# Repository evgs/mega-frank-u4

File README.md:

# MEGAFRANK 1.02-U4
MegaFRANK is a hardware emulation platform built around the Raspberry Pi RP2350 QFN module

## DISCLAIMER 
This megafrank-u4 board is a sub-fork from https://github.com/rh1tech/frank repository originally designed by [Mikhail Matveev](https://github.com/xtremespb), [r1tech](https://github.com/rh1tech)

## Changes
- Two stacked USB-A ports were added on front board edge. 4 USB-A host ports total
- Power barrel 5mm connector was moved to right edge of the board
- ESP-RESET connected to PGPIO36 (optional, available if S11 jumper is closed) 

## DIP Switches S1 description
| Switch | Function                                                   |
| ------ | ---------------------------------------------------------- |
| TDA    | Sound path through I2S TDA (On) or PWM (Off)               |
| TS     | Enable TurboSound path (On)                                |
| TAPE   | Connect TAPE IN analog input to RP2540B                    |
| MONO   | Mono (On) of Stereo (Off) sound path                       |
| MPU    | Enable +3V3 external pullup on GPIO0/1 (Mouse/UART port)   |
| SHDN   | Shutdown (On) speaker amplifier PAM8403 (outputs J13, J14) |

## TDA/TS switches useful combinations
| TDA    | TS     | Output selected        |
| ------ | ------ | ---------------------- |
| off    | off    | RP2350 PWM             |
| **ON** | off    | I2S TDA1387T           |
| off    | **ON** | Turbosound 2xAY-3-8910 |
| **ON** | **ON** | Output Disabled        |

Please read detailed docs in original project [FRANK repository](https://github.com/rh1tech/frank)

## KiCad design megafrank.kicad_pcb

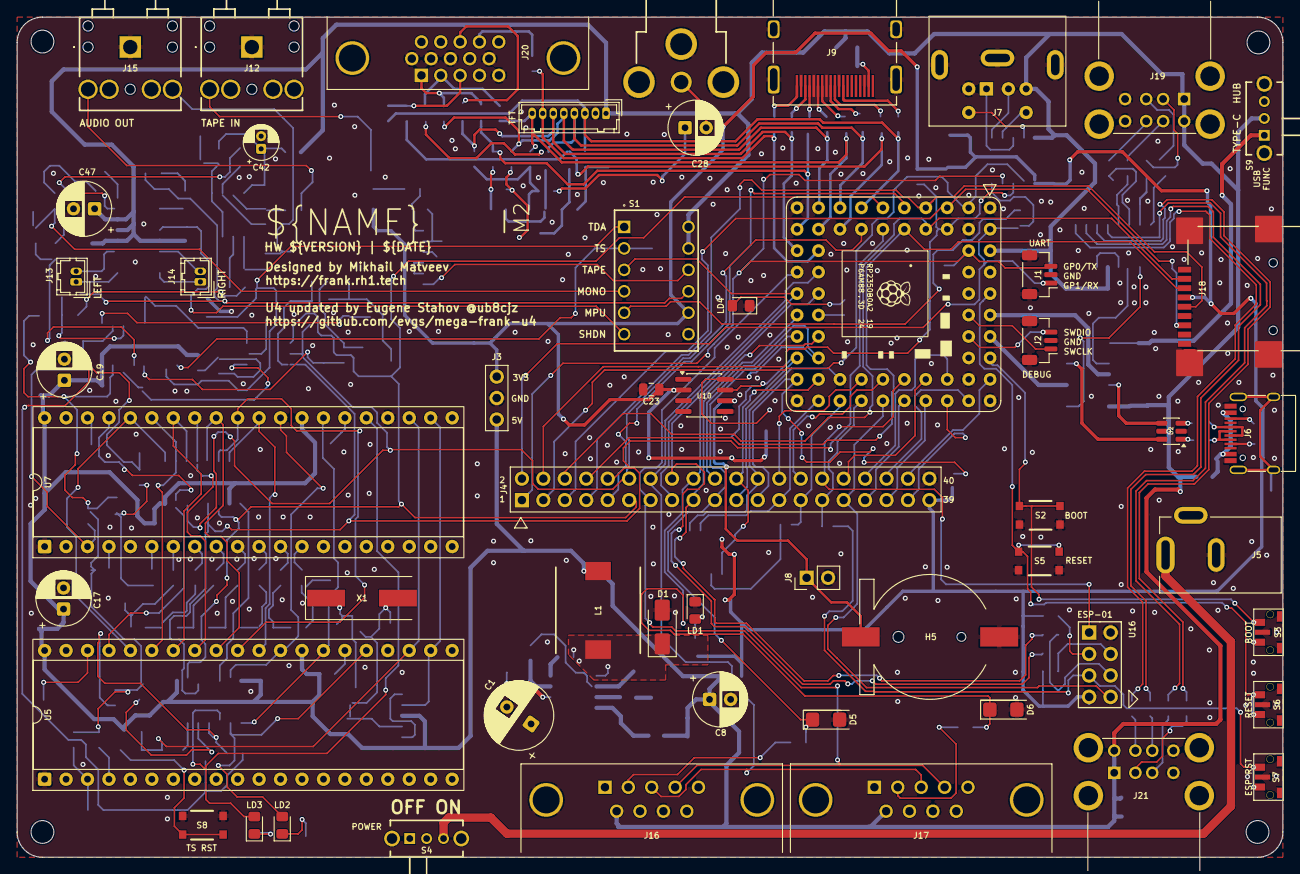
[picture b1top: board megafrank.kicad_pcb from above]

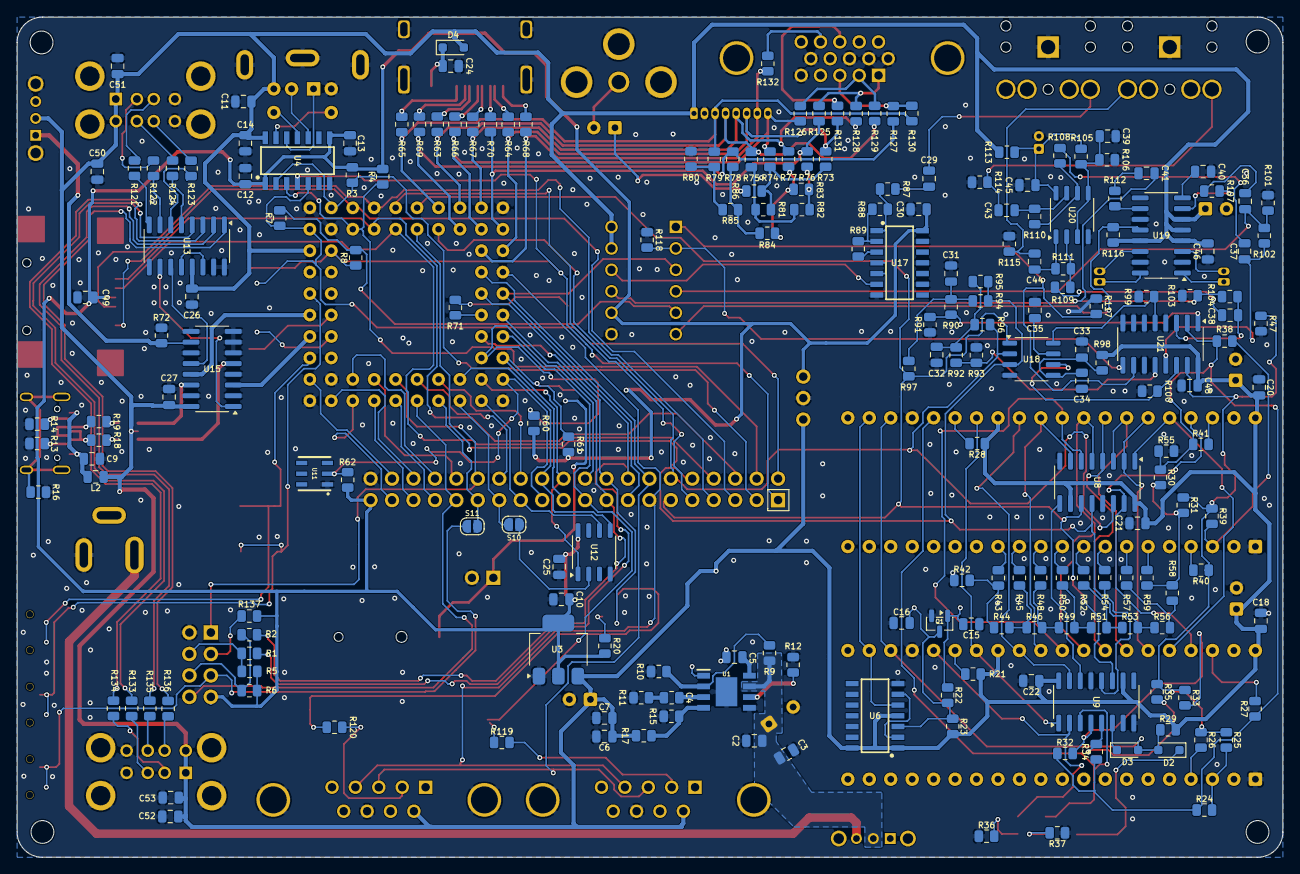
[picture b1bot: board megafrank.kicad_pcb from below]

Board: 2 copper layers, 149.9 x 99.5 mm, 262 parts (204 on the bottom side), 223 nets.

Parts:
C1: 680u; C_Radial_D8.0mm_P3.50mm
C2, C7, C10, C33, C35, C37, C38, C39, C43, C44, C50, C51, C52, C53: 10u; C_0805_2012Metric
C3, C5, C6, C9, C11, C12, C13, C14, C18, C20, C21, C22, C23, C24, C25, C27, C29, C30, C34, C40, C45, C48, C49: 100n; C_0805_2012Metric
C4: 150pF; R_0805_2012Metric
C8, C28: 220u; C_Radial_D6.3mm_P2.50mm
C15, C16: 22p; C_0805_2012Metric
C17, C19, C47: 100u; C_Radial_D6.3mm_P2.50mm
C26: 4.7u; C_0805_2012Metric
C31, C32: 47n; C_0805_2012Metric
C36, C41, C46: 1u; C_0805_2012Metric
C42: 10u; CP_Radial_D4.0mm_P1.50mm
D1: 1N5822; D_SMA
D2, D3: 1N4148; D_SOD-323
D4: 1N5819WS; D_SOD-323
D5, D6: 3V3; D_MiniMELF
H1, H2, H3, H4: Hole 2.7mm; MountingHole_2.7mm
H5: Battery_CR1220
J1: UART; JST_SH_1x03_P1.00mm_Vertical
J2: DEBUG; JST_SH_1x03_P1.00mm_Vertical
J3: PWR; PinHeader_1x03_P2.54mm
J4: Conn_02x20_Odd_Even; PinHeader_2x20_P2.54mm_Vertical
J5: DC-005-5A-2.0; BarrelJack_DC-005
J6: USB4215-03-A; USB_C_Receptacle
J7: MDC-036; MiniDIN_6pin_Female
J8: BAT 3V; PinHeader_1x02_P2.54mm_Vertical
J9: DC3RX19JA2; HDMI_Female
J10: RCA-103; BarrelJack_RCJ-012
J11: Pin Header 1x08; JST_GH_1x08_P1.25mm
J12, J15: SJ1-3525N; AudioJack_3.5mm_SJ1-3525N
J13: PAM L; JST_GH_1x02_P1.25mm
J14: PAM R; JST_GH_1x02_P1.25mm
J16, J17: GP2; DSUB-9_Male_TopMount
J18: 104031-0811; MicroSD_SMD_Long
J19, J21: SS-52100-004; USB_A_Stacked
J20: VGA; DSUB-15_Female
L1: 22uH; Inductor_CDRH104RNP
L2: 330R; C_0805_2012Metric
LD1: Green; LED_0805
LD2, LD3: Orange; LED_0805
LD4: Blue; LED_0805
Q1: BC850; SOT-23
R1, R2, R20, R21, R23, R28, R36, R37, R71, R96, R97, R119, R120, R128, R129, R130: 1K; R_0805_2012Metric
R3, R4, R5, R6, R7, R8, R29, R30, R31, R32, R33, R34, R35, R44, R46, R49, R51, R53, R56, R58, R72, R90, R92, R101, R102, R103, R104, R105, R106, R107, R108, R109, R112, R116, R117, R118, R137: 10K; R_0805_2012Metric
R9, R11, R12, R22, R88, R89: 100K; R_0805_2012Metric
R10: 24K; R_0805_2012Metric
R13, R14: 5.1K; R_0805_2012Metric
R15: 8.2K; R_0805_2012Metric
R16: 1M; R_0805_2012Metric
R17: 43K; R_0805_2012Metric
R18, R19, R121, R122, R123, R124, R133, R134, R135, R136: 22R; R_0805_2012Metric
R24, R25, R38, R39, R60, R61, R62, R87: 4.7K; R_0805_2012Metric
R26, R27, R40, R41, R91, R93, R94, R95: 2K; R_0805_2012Metric
R42, R43, R45, R48, R50, R52, R54, R57, R59, R114, R115: 20K; R_0805_2012Metric
R47, R55: 120R; R_0805_2012Metric
R63, R64, R65, R66, R67, R68, R69, R70, R74, R75, R76, R77, R78, R79: 270R; R_0805_2012Metric
R73: 750R; R_0805_2012Metric
R80: 300R; R_0805_2012Metric
R81, R82, R83, R84, R85: 150R; R_0805_2012Metric
R86: 51R; R_0805_2012Metric
R98, R113, R131, R132: 100R; R_0805_2012Metric
R99, R100: 470R; R_0805_2012Metric
R110, R111: 47K; R_0805_2012Metric
R125, R126, R127: 330R; R_0805_2012Metric
S1: DS01-254-S-06BE
S2: RP BOOT; Button_SMD_3x4x2mm
S3: RP BOOT; Button_SMD_TS1234VW
S4, S9: SK12D07VG3NS; Switch_Slide_SK12D07VG3NS
S5: RP Reset; Button_SMD_3x4x2mm
S6: RP Reset; Button_SMD_TS1234VW
S7: ESP Reset; Button_SMD_TS1234VW
S8: TS Reset; Button_SMD_3x4x2mm
S10: PSRAM On; SolderJumper-2_P1.3mm_Open_RoundedPad1.0x1.5mm
S11: PICO-ESP-RESET; SolderJumper-2_P1.3mm_Open_RoundedPad1.0x1.5mm
U1: MP1584EN-LF-Z; SOIC-9_P1.27mm
U2: USBLC6-2SC6; SOT-23-6
U3: AMS1117 3.3; SOT-223-3_TabPin2
U4: TXS0104EDR; SOIC-14_P1.27mm
U5, U7: JFC95101; DIP-40_W15.24mm_Socket
U6: 74HC74; SOIC-14_P1.27mm
U8, U9: 74HC595; SOP-16_P1.27mm
U10: DS3231MZ; SOIC-8_3.9x4.9mm_P1.27mm
U11: DS2401P+; TSOC-6
U12: ESP-PSRAM64; SO-8
U13: MW7211A; SOP-16_P1.27mm
U14: Pimoroni PGA2350; PGA2350
U15, U21: 74HC4052D; SOP-16_P1.27mm
U16: ESP-01v090; ESP-01S
U17: CD4069UBM; SOIC-14_P1.27mm
U18: TDA1387T; SO-8
U19: PAM8403D; SOP-16_P1.27mm
U20: LM358; SO-8
X1: 3.58 MHz; Crystal_HC49-S

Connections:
+3V3: C10.1, C12.1, C13.1, C23.1, C25.1, C30.1, C49.2, J3.1, J4.39, J18.4 (VDD), R3.2, R4.2, R5.2, R6.2, R20.2, R60.2, R61.2, R62.1, R137.2, S1.11, U3.2 (VO), U4.1 (VCCA), U4.8 (OE), U10.2 (VCC), U12.8 (VCC), U16.7 (VCC), U17.14 (VDD)
/Audio Multiplexer/AMP_IN_L: C37.1, R102.1, U21.13 (1Z)
/Audio Multiplexer/AMP_IN_R: C38.1, R104.1, U21.3 (2Z)
/Audio Multiplexer/PWM_OUT_L: R92.2, R93.1, U21.12 (1Y0)
/Audio Multiplexer/PWM_OUT_R: R90.2, R91.1, U21.1 (2Y0)
/Audio Multiplexer/SW_TDA: R117.2, S1.1, U21.10 (S0)
/Audio Multiplexer/SW_TS: R118.2, S1.2, U21.9 (S1)
/Audio Multiplexer/TDA_L: R100.2, U18.6 (A_LEFT), U21.14 (1Y1)
/Audio Multiplexer/TDA_R: R99.1, U18.8 (A_RIGHT), U21.5 (2Y1)
/Audio/AMP_OUTL: C43.2, J15.2 (TIP), R114.2
/Audio/AMP_OUTR: C44.2, J15.3 (RING), R115.2
/Audio/AMP_PAM_OUTL_M: J13.2, U19.3 (-OUTL)
/Audio/AMP_PAM_OUTL_P: J13.1, U19.1 (+OUT_L)
/Audio/AMP_PAM_OUTR_M: J14.2, U19.14 (-OUT_R)
/Audio/AMP_PAM_OUTR_P: J14.1, U19.16 (+OUT_R)
/Audio/TS/A1: R26.2, U5.4 (B)
/Audio/TS/A2: R40.2, U7.4 (B)
/Audio/TS/B1: R24.2, R25.2, U5.3 (A)
/Audio/TS/B2: R38.2, R39.2, U7.3 (A)
/Audio/TS/BEEP: R32.2, R33.2, U9.4 (QE)
/Audio/TS/C1: R27.2, U5.38 (C)
/Audio/TS/C2: R41.2, U7.38 (C)
/Audio/TS/CLK_1.75M: U5.22 (CLOCK), U6.5 (Q), U7.22 (CLOCK)
/Audio/TS/COVOX_OUT: R30.2, R31.2, R58.2, R59.1
/Audio/TS/DA0: U5.37 (DA0), U7.37 (DA0), U8.15 (QA)
/Audio/TS/DA1: U5.36 (DA1), U7.36 (DA1), U8.1 (QB)
/Audio/TS/DA2: U5.35 (DA2), U7.35 (DA2), U8.2 (QC)
/Audio/TS/DA3: U5.34 (DA3), U7.34 (DA3), U8.3 (QD)
/Audio/TS/DA4: U5.33 (DA4), U7.33 (DA4), U8.4 (QE)
/Audio/TS/DA5: U5.32 (DA5), U7.32 (DA5), U8.5 (QF)
/Audio/TS/DA6: U5.31 (DA6), U7.31 (DA6), U8.6 (QG)
/Audio/TS/DA7: U5.30 (DA7), U7.30 (DA7), U8.7 (QH)
/Audio/TS/DAC0: R43.2, U7.13 (IOB0)
/Audio/TS/DAC1: R45.2, U7.12 (IOB1)
/Audio/TS/DAC2: R48.2, U7.11 (IOB2)
/Audio/TS/DAC3: R50.2, U7.10 (IOB3)
/Audio/TS/DAC4: R52.2, U7.9 (IOB4)
/Audio/TS/DAC5: R54.2, U7.8 (IOB5)
/Audio/TS/DAC6: R57.2, U7.7 (IOB6)
/Audio/TS/DAC7: R59.2, U7.6 (IOB7)
/Audio/TS/L_IN: R25.1, R26.1, R31.1, R33.1, R35.1, R39.1, R40.1, R47.1, U21.15 (1Y2)
/Audio/TS/R_IN: R24.1, R27.1, R30.1, R32.1, R34.1, R38.1, R41.1, R55.1, U21.2 (2Y2)
/Audio/TS/SAVE: R34.2, R35.2, U9.5 (QF)
/Audio/TS/YM_BC1: U5.29 (BC1), U7.29 (BC1), U9.15 (QA)
/Audio/TS/YM_BDIR: U5.27 (BDIR), U7.27 (BDIR), U9.1 (QB)
/Audio/TS/YM_CS1: LD2.2 (A), U5.25 (A8), U9.2 (QC)
/Audio/TS/YM_CS2: LD3.2 (A), U7.25 (A8), U9.3 (QD)
/Audio/TS/YM_RST: D2.2 (A), D3.2 (A), R29.1, U5.23 (~RESET), U7.23 (~RESET)
/Audio/TS/YM_SEL1: R21.2, U5.26 (~SEL)
/Audio/TS/YM_SEL2: R28.2, U7.26 (~SEL)
/Composite/CVBS: C28.2, J10.1
/ESP01S/CH_PD: R137.1, U16.3 (CH_PD)
/ESP01S/GPIO0: R2.1, R6.1, U16.6 (GPIO0)
/ESP01S/GPIO2: R1.1, R5.1, U16.4 (GPIO2)
/ESPRST: S7.1, S11.1 (A), U16.5 (RST)
/MONO_L: C36.1, R101.1, R102.2, S1.4
/MONO_R: C41.1, R103.1, R104.2, S1.10
/MSPUP3V3: R7.2, R8.2, S1.5
/PBOOTSEL: S2.1, S2.3, S3.1, U14.51 (BOOTSEL)
/PGPIO0: J1.1, J4.1, R8.1, U4.4 (A3), U14.61 (GP0)
/PGPIO1: J1.3, J4.2, R7.1, U4.5 (A4), U14.62 (GP1)
/PGPIO2: J4.3, R3.1, U4.2 (A1), U14.2 (GP2)
/PGPIO3: J4.4, R4.1, U4.3 (A2), U14.3 (GP3)
/PGPIO4: J4.5, J18.7 (DAT0), U14.4 (GP4)
/PGPIO5: J4.6, J18.2 (DAT3/CD), U14.5 (GP5)
/PGPIO6: J4.7, J18.5 (CLK), U14.6 (GP6)
/PGPIO7: J4.8, J18.3 (CMD), U14.7 (GP7)
/PGPIO8: J4.9, U14.8 (GP8)
/PGPIO9: J4.10, R94.1, R95.1, U8.12 (RCLK), U9.12 (RCLK), U14.9 (GP9), U18.3 (DATA)
/PGPIO10: J4.11, R97.2, U8.11 (SRCLK), U9.11 (SRCLK), U14.10 (GP10), U18.1 (SCLK)
/PGPIO11: J4.12, R96.2, U8.14 (SER), U14.11 (GP11), U18.2 (LRCK)
/PGPIO12: J11.3, R65.2, R79.1, R130.1, U14.12 (GP12)
/PGPIO13: R69.2, R78.1, R127.1, U14.13 (GP13)
/PGPIO14: J11.4, R63.2, R75.1, R129.1, U14.14 (GP14)
/PGPIO15: J11.8, R66.2, R74.1, R126.1, U14.15 (GP15)
/PGPIO16: J11.5, R67.2, R77.1, R128.1, U14.16 (GP16)
/PGPIO17: R70.2, R76.1, R125.1, U14.17 (GP17)
/PGPIO18: J11.6, R64.2, R73.1, R131.2, U14.19 (GP18)
/PGPIO19: J11.7, R68.2, R132.2, U14.20 (GP19)
/PGPIO20: J4.13, J16.4, J17.4, U14.21 (GP20)
/PGPIO21: J4.14, J16.3, J17.3, U14.22 (GP21)
/PGPIO22: J4.15, S1.3, U14.23 (GP22)
/PGPIO23: J4.16, R1.2, U14.24 (GP23)
/PGPIO24: J4.17, R2.2, U14.25 (GP24)
/PGPIO26: D5.1 (K), J4.19, R119.1, U14.27 (GP26)
/PGPIO27: D6.1 (K), J4.18, R120.1, U14.28 (GP27)
/PGPIO28: J4.21, R61.1, U10.7 (SDA), U14.29 (GP28)
/PGPIO29: J4.20, R60.1, U10.8 (SCL), U14.30 (GP29)
/PGPIO30: J4.23, R62.2, U11.2 (DATA), U14.31 (GP30)
/PGPIO31: J4.22, U12.1 (~CE), U14.32 (GP31)
/PGPIO32: J4.25, U12.6 (SCLK), U14.34 (GP32)
/PGPIO33: J4.24, U12.5 (SI/SIO), U14.35 (GP33)
/PGPIO34: J4.27, S10.2 (B), U14.36 (GP34)
/PGPIO35: J4.26, U14.37 (GP35)
/PGPIO36: J4.29, S11.2 (B), U14.38 (GP36)
/PGPIO37: J4.28, U14.39 (GP37)
/PGPIO38: J4.31, U14.40 (GP38), U16.8 (URXD)
/PGPIO39: J4.30, U14.41 (GP39), U16.1 (UTXD)
/PGPIO40: J4.33, U14.42 (GP40)
/PGPIO41: J4.32, U14.43 (GP41)
/PGPIO42: J4.35, U14.44 (GP42)
/PGPIO43: J4.34, U14.45 (GP43)
/PGPIO44: J4.37, U14.46 (GP44)
/PGPIO45: J4.36, U14.47 (GP45)
/PGPIO46: J4.38, U14.49 (GP46)
/PRUN: S5.1, S5.3, S6.1, U14.56 (RUN)
/PS2/KB_CLK_5V: J7.5, U4.13 (B1)
/PS2/KB_DATA_5V: J7.1, U4.12 (B2)
/PS2/MS_CLK_5V: J7.6, U4.11 (B3)
/PS2/MS_DATA_5V: J7.2, U4.10 (B4)
/PSWCLK: J2.3, U14.55 (SWCLK)
/PSWDIO: J2.1, U14.52 (SWDIO)
/Power/D+: J6.6 (DP1), J6.8 (DP2), R19.2
/Power/D-: J6.5 (DN2), J6.7 (DN1), R18.2
/Power/DM: U2.6 (I/O1), U15.5 (2Y1)
/Power/DP: U2.4 (I/O2), U15.14 (1Y1)
/Power/VBUS_IN: C1.1, C2.1, C3.1, R9.2, S4.2, U1.7 (VIN)
/SHND: R116.2, S1.6, U19.12 (SHND)
/TC_DM: U14.53 (USB_DM), U15.3 (2Z)
/TC_DP: U14.54 (USB_DP), U15.13 (1Z)
/Tape In/LOAD_IN: S1.9, U17.6 (I=*C)
/Tape In/TAPE: C29.2, J12.2 (TIP)
/UM_SW: R72.2, S9.1, U15.10 (S0)
/USB Hub/DM1: R122.1, U13.7 (DM3)
/USB Hub/DM2: R124.1, U13.5 (DM2)
/USB Hub/DM3: R134.1, U13.3 (DM1)
/USB Hub/DM4: R136.1, U13.1 (DM0)
/USB Hub/DM_IN: U13.10 (DMU), U15.1 (2Y0)
/USB Hub/DP1: R121.1, U13.8 (DP3)
/USB Hub/DP2: R123.1, U13.6 (DP2)
/USB Hub/DP3: R133.1, U13.4 (DP1)
/USB Hub/DP4: R135.1, U13.2 (DP0)
/USB Hub/DP_IN: U13.11 (DPU), U15.12 (1Y0)
GND: C1.2, C2.2, C3.2, C6.1, C7.2, C8.2, C9.2, C10.2, C11.2, C12.2, C13.2, C14.2, C15.1, C16.1, C17.2, C18.2, C19.2, C20.2, C21.2, C22.2, C23.2, C24.2, C25.2, C26.2, C27.1, C30.2, C31.2, C32.2, C33.2, C34.2, C35.2, C39.1, C40.2, C42.2, C45.1, C46.2, C47.2, C48.1, C49.1, C50.2, C51.2, C52.2, C53.2, D1.2 (A), D5.2 (A), D6.2 (A), H5.2 (-), J1.2, J2.2, J3.2, J4.40, J5.2, J6.1 (GND), J6.12 (GND), J7.3, J8.2, J9.2 (G_D2), J9.5 (G_D1), J9.8 (G_D0), J9.11 (G_CLK), J9.17 (G_DDC/CEC), J9.20 (SHIELD1), J9.21 (SHIELD2), J9.22 (SHIELD3), J9.23 (SHIELD4), J10.2, J11.2, J12.1 (SLEEVE), J15.1 (SLEEVE), J16.8, J17.8, J18.6 (VSS), J18.SH (SHIELD), J19.4 (GND1), J19.8 (GND2), J19.SH (Shield), J20.0, J20.5, J20.6, J20.7, J20.8, J20.10, J21.4 (GND1), J21.8 (GND2), J21.SH (Shield), LD1.1 (K), LD4.1 (K), Q1.2 (E), R10.2, R11.2, R12.2, R13.1, R14.1, R15.1, R16.1, R36.1, R37.1, R42.1, R47.2, R55.2, R72.1, R80.1, R91.2, R93.2, R99.2, R100.1, R101.2, R103.2, R106.1, R114.1, R115.1, R117.1, R118.1, S1.12, S2.2, S2.4, S3.2, S3.3 (GND), S5.2, S5.4, S6.2, S6.3 (GND), S7.2, S7.3 (GND), S8.2, S8.4, S9.4 (MH1), S9.5 (MH2), U1.5 (GND), U1.9 (EP), U2.2 (GND), U3.1 (GND), U4.7 (GND), U5.1 (VSS), U5.24 (~A9), U6.7 (GND), U7.1 (VSS), U7.24 (~A9), U8.8 (GND), U8.13 (~OE), U9.8 (GND), U9.13 (~OE), U10.5 (GND), U11.1 (GND), U12.4 (VSS), U13.15 (GND), U13.16 (GND), U14.1 (GND), U14.18 (GND), U14.33 (GND), U14.48 (GND), U15.2 (2Y2), U15.4 (2Y3), U15.6 (~E), U15.7 (VEE), U15.8 (GND), U15.9 (S1), U15.11 (1Y3), U15.15 (1Y2), U16.2 (GND), U17.7 (VSS), U17.9 (D14), U17.11 (E), U17.13 (F), U18.4 (AGND), U19.2 (PGND), U19.11 (GND), U19.15 (PGND), U20.4 (V-), U21.4 (2Y3), U21.6 (~E), U21.7 (VEE), U21.8 (GND), U21.11 (1Y3)
GP25: R71.2, U14.26 (GP25)
unnamed: C4.2, R11.1
unnamed: C9.1, J6.2 (VBUS), J6.11 (VBUS), L2.2
unnamed: C28.1, R86.2
unnamed: C29.1, R87.2
unnamed: C31.1, R90.1, R94.2, R97.1
unnamed: C32.1, R92.1, R95.2, R96.1
unnamed: C36.2, R107.2
unnamed: C37.2, R108.2
unnamed: C38.2, R109.2
unnamed: C41.2, R112.2
unnamed: C43.1, R110.1, U20.7
unnamed: C44.1, R111.1, U20.1
unnamed: C5.2, D1.1 (K), L1.1, U1.1 (SW)
unnamed: D2.1 (K), S8.1, S8.3
unnamed: D3.1 (K), U9.6 (QG)
unnamed: C24.1, D4.1 (K), J9.18 (+5V)
unnamed: H5.1 (+), J8.1, U10.6 (VBAT)
unnamed: J5.1, S4.3
unnamed: J6.4 (CC1), R13.2
unnamed: J6.10 (CC2), R14.2
unnamed: J6.13 (SHIELD), R16.2
unnamed: J9.12 (CLKN), R65.1
unnamed: J9.10 (CLKP), R69.1
unnamed: J9.9 (D0N), R63.1
unnamed: J9.7 (D0P), R66.1
unnamed: J9.6 (D1N), R67.1
unnamed: J9.4 (D1P), R70.1
unnamed: J9.3 (D2N), R64.1
unnamed: J9.1 (D2P), R68.1
unnamed: J16.2, R119.2
unnamed: J17.2, R120.2
unnamed: J19.3 (D1+), R121.2
unnamed: J19.2 (D1-), R122.2
unnamed: J19.7 (D2+), R123.2
unnamed: J19.6 (D2-), R124.2
unnamed: J20.1, R125.2, R128.2
unnamed: J20.2, R126.2, R129.2
unnamed: J20.3, R127.2, R130.2
unnamed: J20.13, R131.1
unnamed: J20.14, R132.1
unnamed: J21.3 (D1+), R133.2
unnamed: J21.2 (D1-), R134.2
unnamed: J21.7 (D2+), R135.2
unnamed: J21.6 (D2-), R136.2
unnamed: LD1.2 (A), R20.1
unnamed: LD2.1 (K), R36.2
unnamed: LD3.1 (K), R37.2
unnamed: LD4.2 (A), R71.1
unnamed: C15.2, Q1.1 (B), R22.1, X1.1
unnamed: C16.2, Q1.3 (C), R22.2, R23.1, U6.3 (C), X1.2
unnamed: R18.1, U2.1 (I/O1)
unnamed: R19.1, U2.3 (I/O2)
unnamed: R42.2, R43.1, R44.1
unnamed: R44.2, R45.1, R46.1
unnamed: R46.2, R48.1, R49.1
unnamed: R49.2, R50.1, R51.1
unnamed: R51.2, R52.1, R53.1
unnamed: R53.2, R54.1, R56.1
unnamed: R56.2, R57.1, R58.1
unnamed: R73.2, R74.2, R81.2, R86.1
unnamed: R75.2, R81.1, R82.2
unnamed: R76.2, R82.1, R83.2
unnamed: R77.2, R83.1, R84.2
unnamed: R78.2, R84.1, R85.2
unnamed: R79.2, R80.2, R85.1
unnamed: S10.1 (A), U12.2 (SO/SIO)
unnamed: C5.1, U1.8 (BST)
unnamed: C4.1, U1.3 (COMP)
unnamed: R9.1, R10.1, U1.2 (EN)
unnamed: R15.2, R17.2, U1.4 (FB)
unnamed: R12.1, U1.6 (FREQ)
unnamed: U6.2 (D), U6.6 (~Q)
unnamed: U8.9 (QH'), U9.14 (SER)
unnamed: U13.12 (VD33), U13.14 (VD3)
unnamed: R87.1, R88.2, U17.1 (A)
unnamed: R89.1, U17.3 (B)
unnamed: U17.4 (H=*B), U17.5 (C)
unnamed: R88.1, R89.2, U17.2 (G-*A)
unnamed: C35.1, U18.7 (FLT)
unnamed: C33.1, C34.1, R98.1, U18.5 (VA)
unnamed: R107.1, U19.7 (INL)
unnamed: R112.1, U19.10 (INR)
unnamed: C40.1, U19.8 (VREF)
unnamed: C39.2, R105.1, R106.2, U20.3 (+), U20.5 (+)
unnamed: R109.1, R111.2, U20.2 (-)
unnamed: R108.1, R110.2, U20.6 (-)
unnamed: C42.1, C45.2, R105.2, R113.2, U20.8 (V+)
VBUS: C6.2, C7.1, C8.1, C11.1, C14.1, C17.1, C18.1, C19.1, C20.1, C21.1, C22.1, C26.1, C27.2, C46.1, C47.1, C48.2, C50.1, C51.1, C52.1, C53.1, D4.2 (A), J3.3, J7.4, J11.1, J16.6, J17.6, J19.1 (VBUS1), J19.5 (VBUS2), J21.1 (VBUS1), J21.5 (VBUS2), L1.2, L2.1, R17.1, R21.1, R23.2, R28.1, R29.2, R98.2, R113.1, R116.1, S1.7, S1.8, S9.2, U2.5 (VBUS), U3.3 (VI), U4.14 (VCCB), U5.28 (BC2), U5.40 (VCC), U6.1 (~R), U6.4 (~S), U6.14 (VCC), U7.28 (BC2), U7.40 (VCC), U8.10 (~SRCLR), U8.16 (VCC), U9.10 (~SRCLR), U9.16 (VCC), U13.13 (VDD5), U14.60 (VBUS), U15.16 (VCC), U19.4 (PVDD), U19.5 (MUTE), U19.6 (VDD), U19.13 (PVDD), U21.16 (VCC)
